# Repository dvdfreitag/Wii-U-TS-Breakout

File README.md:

# Wii-U-TS-Breakout
Wii U touchscreen controller breakout board

The Wii U gamepad uses a [Texas Instruments TSC2046](https://www.digikey.com/product-detail/en/texas-instruments/TSC2046EIPWR/296-41783-1-ND/5224574) 4-wire resistive touch screen controller. 

This board has the same connector as the Wii U touchscreen so the Wii U gamepad display can be used externally.

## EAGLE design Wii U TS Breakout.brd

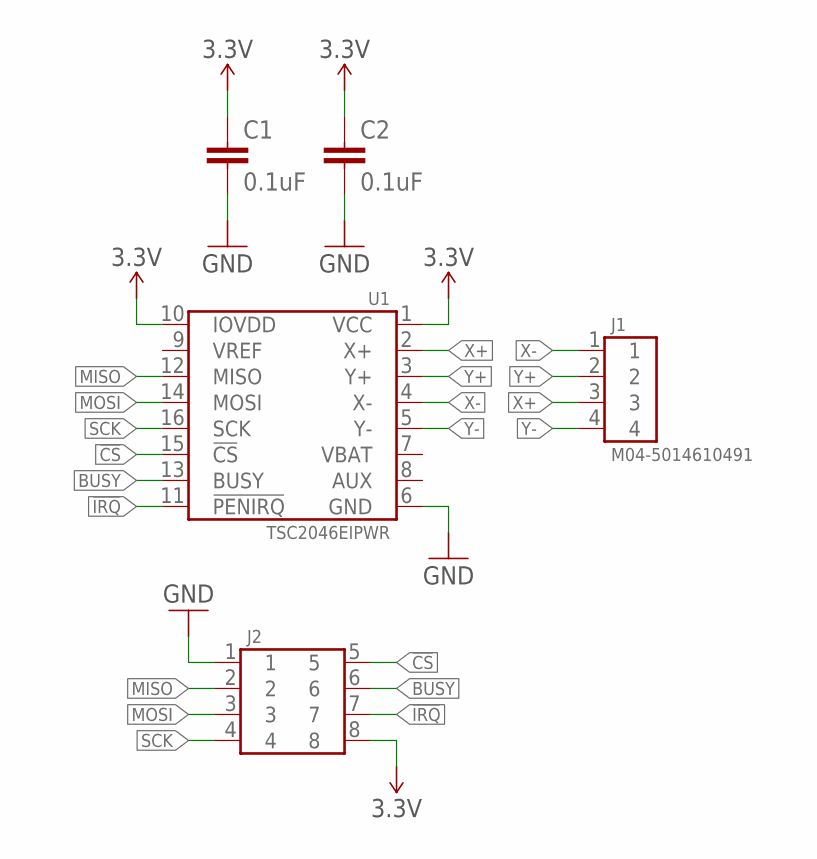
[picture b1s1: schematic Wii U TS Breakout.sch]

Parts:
C1, C2: 0.1uF; 0603-CAP
J1: M04-5014610491; 5014610491
J2: M04X2-100MIL
U1: TSC2046EIPWR; TSSOP-16

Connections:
3.3V: C1.1, C2.1, J2.8, U1.1 (VCC), U1.10 (IOVDD)
!CS: J2.5, U1.15 (!CS)
!IRQ: J2.7, U1.11 (!PENIRQ)
BUSY: J2.6, U1.13 (BUSY)
GND: C1.2, C2.2, J2.1, U1.6 (GND)
MISO: J2.2, U1.12 (MISO)
MOSI: J2.3, U1.14 (MOSI)
SCK: J2.4, U1.16 (SCK)
X+: J1.3, U1.2 (X+)
X-: J1.1, U1.4 (X-)
Y+: J1.2, U1.3 (Y+)
Y-: J1.4, U1.5 (Y-)

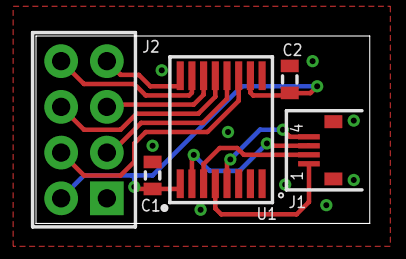
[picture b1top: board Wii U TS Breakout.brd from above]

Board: 2 copper layers, 18.5 x 10.4 mm, 5 parts (0 on the bottom side), 12 nets.

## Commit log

2018-02-06 :circus_tent: Added .gitattributes
2018-02-07 Create LICENSE
